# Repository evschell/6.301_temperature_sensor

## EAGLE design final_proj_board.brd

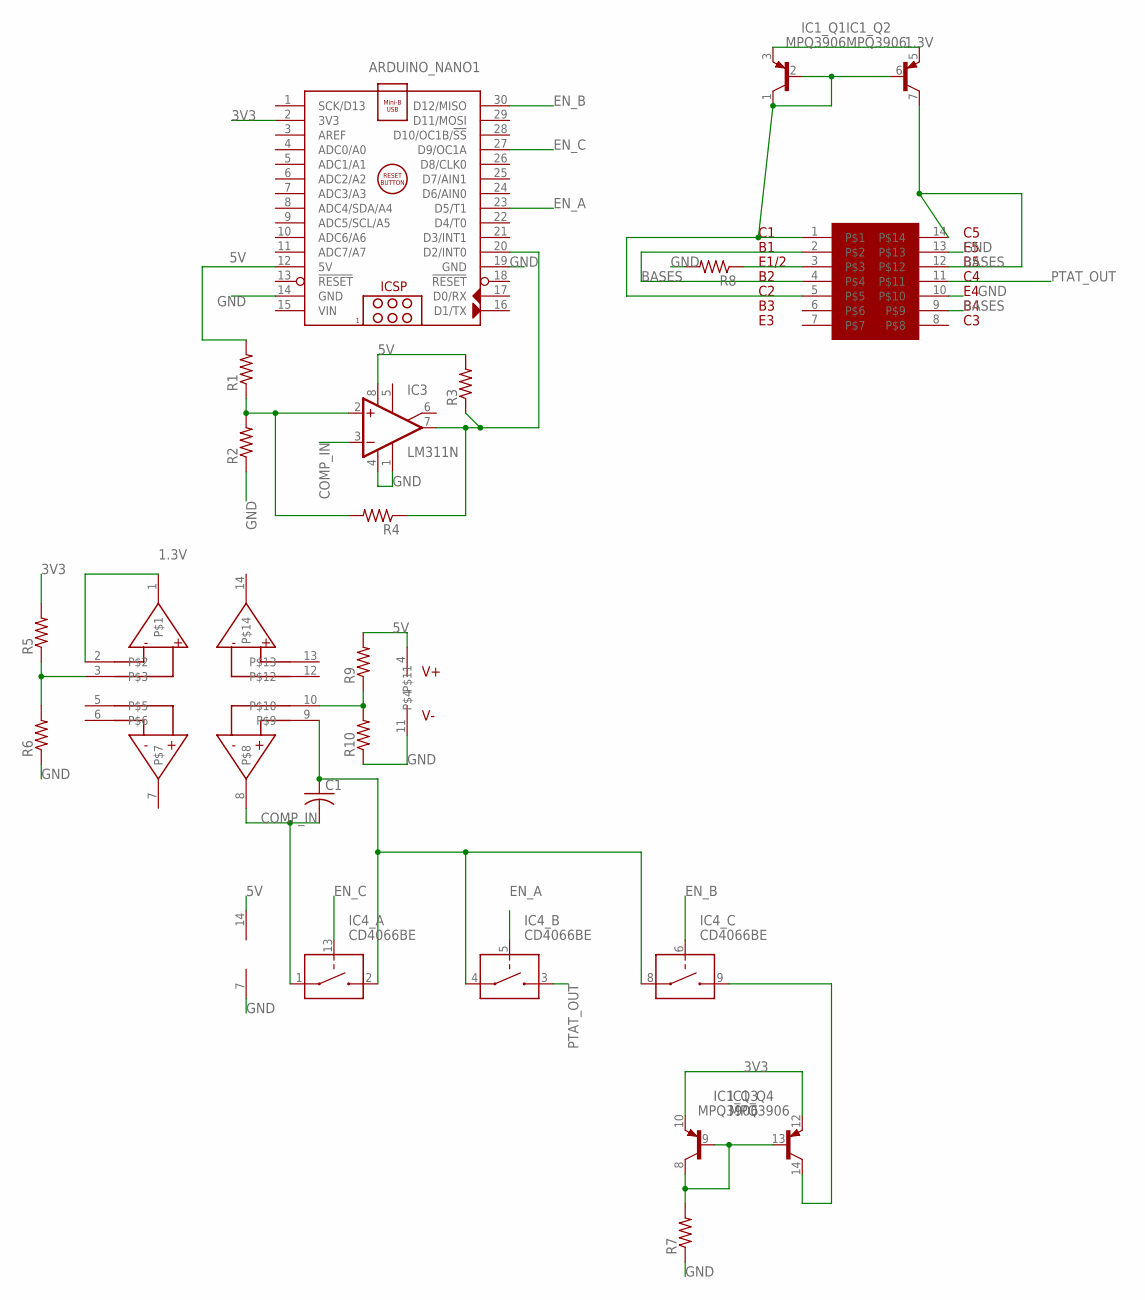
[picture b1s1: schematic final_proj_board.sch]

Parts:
ARDUINO_NANO1: ARDUINO_NANO
C1: C-US050-024X044; C050-024X044
IC1: MPQ3906; DIL14
IC2: CA3046; DIL14
IC3: LM311N; DIL08
IC4: CD4066BE; DIL14
R1, R2, R3, R4, R5, R6, R7, R8, R9, R10: R-US_0204/7; 0204/7
U$1: LM6134; DIL14

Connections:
1.3V: IC1.3 (E), IC1.5 (E), U$1.1, U$1.2
3V3: ARDUINO_NANO1.2 (3V3), IC1.10 (E), IC1.12 (E), R5.2
5V: ARDUINO_NANO1.12 (5V), IC3.8 (V+), IC4.14 (V+), R1.2, R3.2, R9.2, U$1.4
BASES: IC1.7 (C), IC2.2, IC2.4, IC2.9, IC2.12, IC2.14
COMP_IN: C1.2, IC3.3 (-IN), IC4.1 (IN/OUT1), U$1.8
EN_A: ARDUINO_NANO1.23 (D5/T1), IC4.5 (CONTROL)
EN_B: ARDUINO_NANO1.30 (D12/MISO), IC4.6 (CONTROL)
EN_C: ARDUINO_NANO1.27 (D9/OC1A), IC4.13 (CONTROL)
GND: ARDUINO_NANO1.14 (GND), ARDUINO_NANO1.19 (GND), IC2.10, IC2.13, IC3.1 (GND), IC3.4 (V-), IC4.7 (V-), R2.1, R6.1, R7.1, R8.2, R10.1, U$1.11
unnamed: IC2.3, R8.1
unnamed: IC1.1 (C), IC1.2 (B), IC1.6 (B), IC2.1, IC2.5
unnamed: ARDUINO_NANO1.20 (D2/INT0), IC3.7 (OUT), R3.1, R4.1
unnamed: IC3.2 (+IN), R1.1, R2.2, R4.2
unnamed: R9.1, R10.2, U$1.10
unnamed: C1.1, IC4.2 (IN/OUT2), IC4.4 (IN/OUT1), IC4.8 (IN/OUT1), U$1.9
unnamed: IC1.8 (C), IC1.9 (B), IC1.13 (B), R7.2
unnamed: R5.1, R6.2, U$1.3
unnamed: IC1.14 (C), IC4.9 (IN/OUT2)
PTAT_OUT: IC2.11, IC4.3 (IN/OUT2)
VIN: ARDUINO_NANO1.15 (VIN)

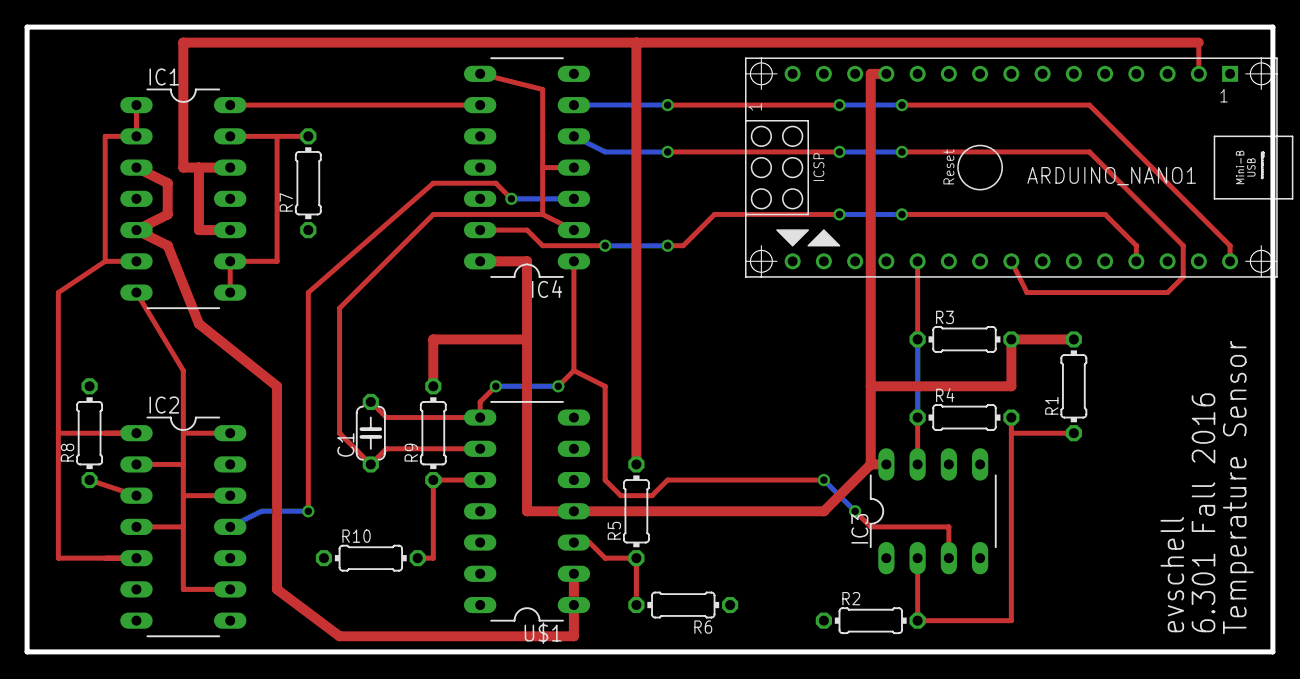
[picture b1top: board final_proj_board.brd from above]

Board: 2 copper layers, 101.3 x 50.8 mm, 17 parts (0 on the bottom side), 19 nets.

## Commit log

2016-12-12 Rename final_proj_firmware.ino to firmware/final_proj_firmware.ino
2016-12-12 Rename final_proj_board.b#1 to design_files/final_proj_board.b#1
2016-12-12 Rename final_proj_board.b#2 to design_files/final_proj_board.b#2
2016-12-12 Rename final_proj_board.b#3 to design_files/final_proj_board.b#3
2016-12-12 Rename final_proj_board.b#4 to design_files/final_proj_board.b#4
2016-12-12 Rename final_proj_board.b#5 to design_files/final_proj_board.b#5
2016-12-12 Rename final_proj_board.b#6 to design_files/final_proj_board.b#6
2016-12-12 Rename final_proj_board.b#7 to design_files/final_proj_board.b#7
2016-12-12 Rename final_proj_board.b#8 to design_files/final_proj_board.b#8
2016-12-12 Rename final_proj_board.b#9 to design_files/final_proj_board.b#9
2016-12-12 Rename final_proj_board.cmp to gerb/final_proj_board.cmp
2016-12-12 Rename final_proj_board.sol to gerb/final_proj_board.sol
2016-12-12 Rename final_proj_board.stc to gerb/final_proj_board.stc
2016-12-12 Rename final_proj_board.sch to design_files/final_proj_board.sch
2016-12-12 Rename final_proj_board.brd to design_files/final_proj_board.brd
2016-12-12 Rename final_proj_board.drd to gerb/final_proj_board.drd
2016-12-12 Rename final_proj_board.dri to gerb/final_proj_board.dri
2016-12-12 Rename final_proj_board.gpi to gerb/final_proj_board.gpi
2016-12-12 Rename final_proj_board.plc to gerb/final_proj_board.plc
2016-12-12 Rename final_proj_board.pro to gerb/final_proj_board.pro
2016-12-12 Rename final_proj_board.sts to gerb/final_proj_board.sts
